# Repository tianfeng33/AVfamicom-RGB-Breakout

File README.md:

# AVfamicom-RGB-Breakout
This is a simple break out board designed to be used with Tim Worthingtons's NES RGB
The goal of this was to create a board where you would be able to plug in headers and easily connect to the nesrgb without having to solder directly to the din or to flip the board over. 
Thanks to Mobius for help with the measurments.

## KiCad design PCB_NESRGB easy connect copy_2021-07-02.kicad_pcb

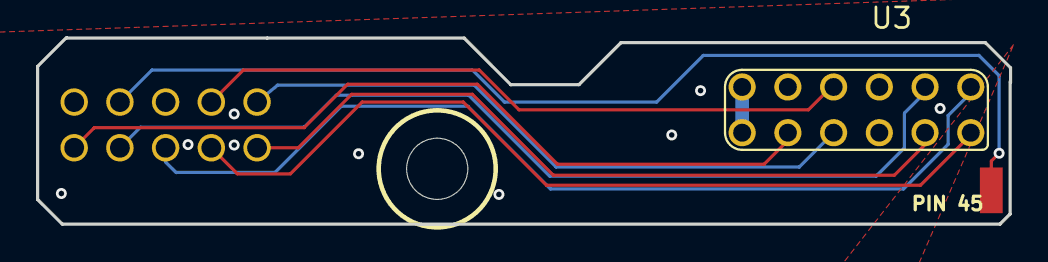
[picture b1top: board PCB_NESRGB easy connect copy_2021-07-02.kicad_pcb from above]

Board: 2 copper layers, 54.1 x 10.4 mm, 4 parts (0 on the bottom side), 10 nets.

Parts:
P1: 2.54-2X5
R: _; SMD1,27-2,54
U2: MOUNTINGHOLE-M3
U3: SNES MULTI

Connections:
A: P1.2, R.1
AUDIO: U3.11, U3.12
B: P1.1, U3.4
C: P1.6, U3.8
G: P1.3, U3.2
GND: P1.4, U3.5, U3.6
R: P1.5, U3.1
S: P1.7, U3.3
V: P1.1, U3.9
Y: P1.8, U3.7

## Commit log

2021-07-02 Easyeda and converted KiCAD design files.
